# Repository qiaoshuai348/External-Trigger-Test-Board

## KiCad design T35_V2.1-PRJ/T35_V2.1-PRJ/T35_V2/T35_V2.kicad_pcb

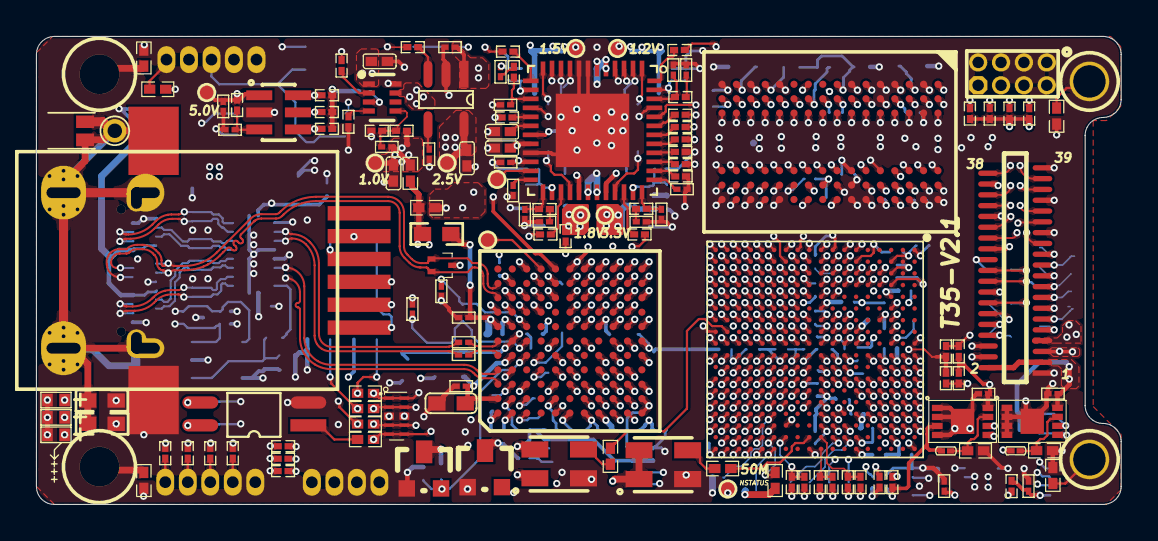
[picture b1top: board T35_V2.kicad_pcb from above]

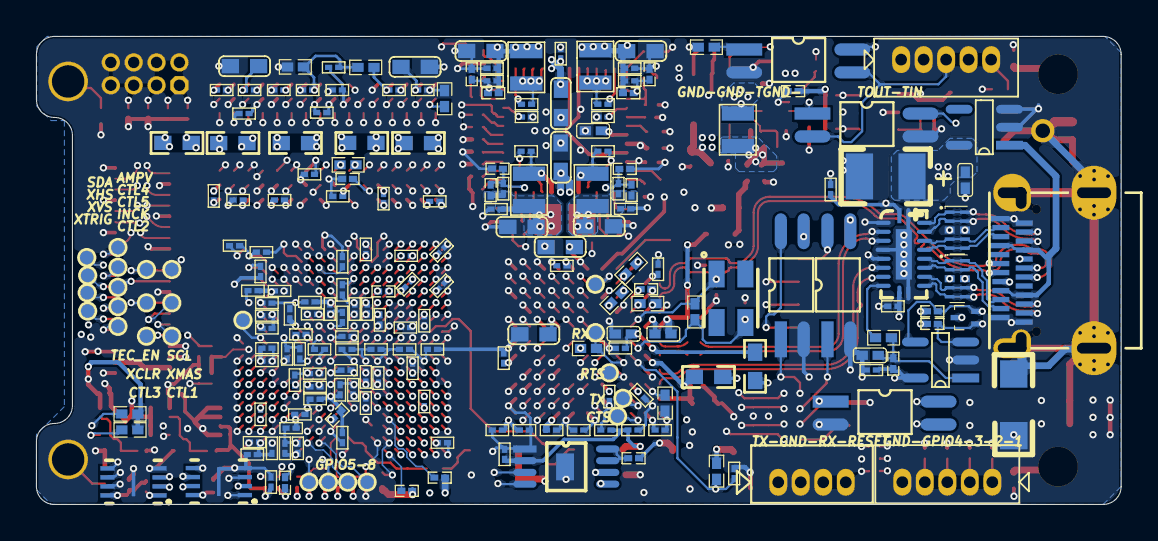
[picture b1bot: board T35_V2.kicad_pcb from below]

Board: 12 copper layers, 60.3 x 26.0 mm, 356 parts (217 on the bottom side), 287 nets.

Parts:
C1, C3, C83, C87, C91, C96: 22pF/6.3V; 0201CS
C2, C4, C7, C9, C11, C14, C16, C18, C22, C25, C28, C30, C31, C33, C35, C38, C39, C42, C43, C45, C47, C49, C52, C55, C58, C63, C66, C68, C77, C80, C85, C88, C93, C94, C98, C99, C104, C111, C112, C113, C115, C117, C119, C120, C123, C125, C127, C128, C129, C130, C131, C134, C135, C136, C137, C138, C139, C140, C141, C154, C155, C156, C157, C158, C159: 100nF/10V; 0201CS
C5, C12, C19, C20, C23, C26, C36, C40, C44, C46, C48, C50, C53, C56, C59, C61, C64: 2.2uF/6.3V; 0201CS
C6, C8, C10, C13, C15, C17, C21, C24, C27, C34, C37, C41, C51, C54, C57, C60, C62, C65, C75, C102: 10nF/16V; 0201CS
C29, C73, C142, C143, C144, C145: 1uF/6.3V; 0201CS
C32, C71, C105, C106: 10uF/6.3V; 0402CS
C67, C72, C110, C122, C126: 4.7uF/6.3V; 0402CS
C69, C70: 22uF/10V; 0603CS
C74: 1nF/6.3V; 0201CS
C76, C79: 33nF/6.3V; 0201CS
C78, C86, C95, C100, C124, C132, C133: 22uF/6.3V; 0603CS
C81, C89, C97, C101: 68pF/6.3V; 0201CS
C82, C84, C90, C92: 4.7nF/6.3V; 0201CS
C103: 10pF/6.3V; 0201CS
C107, C118, C121: 18pF/6.3V; 0201CS
C114: 470pF/2KV; 1206CS
C116: 33pF/6.3V; 0402CS
C146, C147: 47uF/6.3V; 0603CS
C148, C149, C150, C151, C152, C153: 10nF/6.3V; 0201CS
CRY1: 19.2MHZ无源晶振; XTAL_SMD_SMALL
ECP1: 47uF10V; CASE-B
FB1, FB2, FB3, FB4, FB5: FB 600Ω@100MHz; FB0603
FB6: FB*; FB0603
FB7, FB8, FB9: FB 1.8KΩ@100MHz; FB0603
L1, L2, L3, L4: 2.2uH/1.5A; 201610
L5: 0.47uH; 201610
LED1: LED_R; 0402LED
LED2: LED_G; 0402LED
LED3: LED_B; 0402LED
P1: USB3.0_Type-C; CONN_105450-0101_MOL - ENFORCE
P2: 39Pin_MIPI_Connector; 39PIN_0.3错位排序
P3, P5: 1.25mm5Pin; CC125-5
P4: GuiderPort; RJ11-SMD
P6: 1.25mm4Pin; CON_530470410_MOL
P7: JTAG-1.25mm2*4; MHDR2X4
P8: M543-1
PAD1, PAD2: PAD; M2-R4-NC
PAD3, PAD4: PAD; M1.6-R3.2-NC
R1, R2: 33Ω; 0402RS
R3, R5, R6, R7, R8, R9, R10, R12, R15, R16, R17, R18, R20, R21, R22, R25, R26, R28, R30, R31, R32, R36, R40, R43, R44, R46, R50, R51, R53, R67, R84, R93, R101, R102, R103, R104: 10K; 0201RS
R4: 324K; 0402RS
R11, R13, R14, R19, R23: 10K*; 0201RS
R24: 44.2K; 0201RS
R27, R29: 0Ω; 0201RS
R33: 22K; 0201RS
R34: 4.99K; 0201RS
R35, R37, R39, R41: 15.4K; 0201RS
R38: 8.66K; 0201RS
R42: 12.4K; 0201RS
R45: 30.9K; 0201RS
R47, R48, R49: 100K; 0201RS
R52, R57: 0*; 0201RS
R54: 20K; 0201RS
R55: 91K; 0201RS
R56: 30K; 0201RS
R58: 1M; 0603RS
R59, R60, R69, R71, R72: 1.5K; 0402RS
R61: 200 1%; 0402RS
R62: 6.04K 1%; 0402RS
R64, R65: 5.1K; 0201RS
R66: 10Ω; 0402RS
R68: 1.5K*; 0402RS
R70: 200K; 0201RS
R74: 1MΩ*; 0402RS
R75, R79, R80, R88: 1K 1%; 0402RS
R76, R77, R86, R87, R96, R97: 0*; 0402RS
R78: 80.6Ω 1%; 0402RS
R81: 4.7K; 0402RS
R82, R83: 240 1%; 0201RS
R89, R90, R91, R92, R94, R95: 100; 0402RS
R98: 300; 0201RS
R99, R100: 100; 0201RS
SJ1, SJ2: SolderableJumper*; SJ
T1, T2, T3, T4, T5, T6, T8, T9, T10, T11, T12, T13, T14, T15, T16, T17, T18, T19, T20, T21, T22, T23, T24, T25, T26, T27, T28, T29, T30, T31, T32, T33, T34, T35, T36: TP-S
U1: T35F324; T35-F324-BGA100P9X9-81A
U2: 50MHz; XTAL_SMD_SMALL
U3: 100MHz; XTAL_SMD_SMALL
U4, U14: MAX809TTRG; MAX809
U5, U19: GD25Q32EEIGR; SON127P600-8N-USON8
U6: TPS65400RGZT; QFN50P700X700X100-49N_TPS65400RGZT(PRIMARY)
U7: TPS628501DRLR; SOT583
U8: TPS79325DBVR; SOT-23-5
U9: LM3880MF-1AA; SOT-23-6
U10: CYUSB3014-BZXI; CYUSB3014
U11: NCP361SNT1G; SOT-23-5
U12, U30: TPD2EUSB30ADRTR-N; DRT0003A
U13: TLV3201AIDBVR; sot-23-5
U15: UM3212M8; MSOP8
U16: BL24C64A-NTRC; UDFN-8LL
U17: MT41K256M16TW-107:P; MICT-TNA-96
U18: BL24CM1A-NTRC; UDFN-8LL
U20, U22, U23, U24, U25, U26: IS281GB; TLP281-1
U21, U28, U29: RCLAMP0524
U27: CBTL02043ABQ; VQFN-20

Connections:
A0: U1.U15, U10.H5
A1: U1.T17, U10.J5
AMPV: P2.23, T22.1, U1.B10
CBSEL0: R13.2, R20.2, U1.J17
CBSEL1: R14.2, R22.2, U1.J18
CBUS0: R10.2, R19.2, U1.M14
CBUS1: R11.2, R21.2, U1.M16
CBUS2: R12.2, R23.2, U1.M17
CC1: P1.A5, R65.2, U13.3, U30.1
CC2: P1.B5, R64.2, U13.4, U30.2
CCK: U1.N13, U5.6, U19.6
CDI0: U1.M13, U5.5, U19.5
CDI1: U1.N14, U5.2, U19.2
CDI2: R9.1, U1.K14, U5.3, U19.3
CDI3: R5.1, U1.K18, U5.7, U19.7
CDONE: R3.2, U1.N18
CHARGER_DECT: T21.1, U10.D11
CLK_50MHz: R1.2, U1.K17
CLK_OUT: R53.1, U6.44, U7.3
CMOS_CTL1: P2.10, T31.1, U1.B12
CMOS_CTL2: P2.9, T33.1, U1.B16
CMOS_CTL3: P2.8, T35.1, U1.A13
CMOS_CTL4: P2.19, T30.1, U1.A12
CMOS_CTL5: P2.18, T32.1, U1.B11
CRESET_N: P7.8, R4.2, U1.N17, U4.2
CSI: R6.2, U1.N15
CTL1: U1.R13, U10.K7
CTL4: U1.V10, U10.G7
CTL5: U1.U14, U10.G6
CTL6: U1.V16, U10.K6
CTL7: U1.P12, U10.H8
DDR_A0: U1.P3, U17.N3
DDR_A1: U1.P4, U17.P7
DDR_A2: U1.R6, U17.P3
DDR_A3: U1.P6, U17.N2
DDR_A4: U1.T1, U17.P8
DDR_A5: U1.R3, U17.P2
DDR_A6: U1.R7, U17.R8
DDR_A7: U1.V8, U17.R2
DDR_A8: U1.T4, U17.T8
DDR_A9: U1.T3, U17.R3
DDR_A10: U1.V7, U17.L7
DDR_A11: U1.U7, U17.R7
DDR_A12: U1.U6, U17.N7
DDR_A13: U1.T6, U17.T3
DDR_A14: U1.V6, U17.T7
DDR_A15: U1.V5, U17.M7
DDR_BA0: U1.T5, U17.M2
DDR_BA1: U1.U3, U17.N8
DDR_BA2: U1.R5, U17.M3
DDR_CKE: U1.N7, U17.K9
DDR_CK_N: R78.1, U1.R1, U17.K7
DDR_CK_P: R78.2, U1.P1, U17.J7
DDR_DM0: U1.L1, U17.E7
DDR_DM1: U1.H5, U17.D3
DDR_DQ0: U1.N4, U17.E3
DDR_DQ1: U1.N2, U17.F7
DDR_DQ2: U1.N1, U17.F2
DDR_DQ3: U1.M2, U17.F8
DDR_DQ4: U1.M4, U17.H3
DDR_DQ5: U1.L3, U17.H8
DDR_DQ6: U1.K1, U17.G2
DDR_DQ7: U1.L4, U17.H7
DDR_DQ8: U1.J1, U17.D7
DDR_DQ9: U1.K2, U17.C3
DDR_DQ10: U1.J3, U17.C8
DDR_DQ11: U1.K3, U17.C2
DDR_DQ12: U1.J4, U17.A7
DDR_DQ13: U1.H4, U17.A2
DDR_DQ14: U1.J5, U17.B8
DDR_DQ15: U1.G4, U17.A3
DDR_DQS0_N: U1.N3, U17.G3
DDR_DQS0_P: U1.M3, U17.F3
DDR_DQS1_N: U1.L5, U17.B7
DDR_DQS1_P: U1.K5, U17.C7
DDR_ODT: U1.U1, U17.K1
DDR_REFCLK: R2.2, U1.U8
DDR_RST: R81.1, U1.T2, U17.T2
DDR_~CAS: U1.V2, U17.K3
DDR_~CS: U1.N6, U17.L2
DDR_~RAS: U1.V3, U17.J3
DDR_~WE: U1.U4, U17.L3
D_N: P1.A7, P1.B7, U10.A10, U12.1
D_P: P1.A6, P1.B6, U10.A9, U12.2
FLASH_CS: R84.1, U1.G16, U19.1
FPGA_TCK: P7.1, R15.2, U1.T16
FPGA_TDI: P7.3, R17.2, U1.R16
FPGA_TDO: P7.7, R16.2, U1.P17
FPGA_TMS: P7.5, R18.2, U1.P16
FX3_RESET: C117.1, R68.2, U1.D13, U10.C5, U14.2
GND: C1.1, C2.2, C3.1, C4.2, C5.2, C6.2, C7.2, C8.2, C9.2, C10.2, C11.2, C12.2, C13.2, C14.2, C15.2, C16.2, C17.2, C18.2, C19.2, C20.2, C21.2, C22.2, C23.2, C24.2, C25.2, C26.2, C27.2, C28.2, C29.2, C30.2, C31.2, C32.2, C33.2, C34.2, C35.2, C36.2, C37.2, C38.2, C39.2, C40.2, C41.2, C42.2, C43.2, C44.2, C45.2, C46.2, C47.2, C48.2, C49.2, C50.2, C51.2, C52.2, C53.2, C54.2, C55.2, C56.2, C57.2, C58.2, C59.2, C60.2, C61.2, C62.2, C63.2, C64.2, C65.2, C66.2, C67.2, C68.1, C69.1, C70.1, C71.2, C72.2, C73.1, C74.1, C75.1, C76.1, C77.1, C78.2, C79.1, C82.2, C83.2, C84.2, C85.1, C86.2, C87.2, C90.2, C91.2, C92.2, C94.1, C95.2, C96.2, C99.1, C100.2, C102.2, C104.2, C105.2, C106.2, C107.2, C110.1, C112.1, C114.1, C115.1, C116.2, C117.2, C118.1, C119.2, C120.1, C121.2, C122.1, C123.1, C124.1, C125.1, C126.1, C127.1, C128.1, C129.1, C130.1, C131.1, C132.1, C133.1, C134.1, C135.1, C136.1, C137.1, C138.2, C139.2, C140.2, C141.2, C142.2, C143.2, C144.2, C145.2, C146.2, C147.2, C148.2, C149.2, C150.2, C151.2, C152.2, C153.2, C155.2, C156.2, C157.2, C158.1, C159.1, ECP1.2, FB6.1, LED1.2, LED2.2, LED3.2, P1.A1, P1.A12, P1.B1, P1.B12, P2.1, P2.4, P2.6, P2.16, P2.24, P2.27, P2.30, P2.33, P2.36, P2.39, P3.5, P4.0, P5.1, P5.2, P6.2, P7.6, R19.1, R20.1, R21.1, R22.1, R23.1, R24.1, R33.2, R36.2, R40.2, R44.2, R46.2, R55.1, R56.1, R57.1, R58.2, R61.2, R62.2, R64.1, R65.1, R75.2, R80.1, R81.2, R82.2, R83.2, R86.1, R87.1, R88.2, R96.1, R97.1, R101.2, R102.2, R103.2, R104.2, U1.A1, U1.A18, U1.C3, U1.C7, U1.C8, U1.C12, U1.C15, U1.D10, U1.F2, U1.F4, U1.F17, U1.G7, U1.G9, U1.G11, U1.H1, U1.H8, U1.H10, U1.H12, U1.J7, U1.J9, U1.J11, U1.J16, U1.K8, U1.K10, U1.K12, U1.L7, U1.L9, U1.L11, U1.M1, U1.M5, U1.M8, U1.M10, U1.M12, U1.N16, U1.P7, U1.R2, U1.R4, U1.R10, U1.T13, U1.V1, U1.V4, U1.V18, U2.2, U3.2, U4.1, U5.4, U5.9, U6.7, U6.8, U6.21, U6.EP, U7.8, U8.2, U9.2, U10.A1, U10.A8, U10.B2, U10.B4, U10.B7, U10.B8, U10.B9, U10.D8, U10.E2, U10.E6, U10.G1, U10.G11, U10.K3, U10.K4, U10.K8, U10.L1, U10.L2, U10.L3, U10.L6, U10.L11, U11.2, U11.3, U12.3, U13.2, U14.1, U15.1, U15.SS, U16.1, U16.2, U16.3, U16.4, U16.9, U17.A9, U17.B1, U17.B3, U17.B9, U17.D1, U17.D8, U17.E1, U17.E2, U17.E8, U17.F9, U17.G1, U17.G8, U17.G9, U17.J2, U17.J8, U17.M1, U17.M9, U17.P1, U17.P9, U17.T1, U17.T9, U18.1, U18.2, U18.4, U18.9, U19.4, U19.9, U20.2, U21.9, U21.10, U22.2, U23.2, U24.2, U25.3, U26.2, U27.2, U27.5, U27.11, U27.20, U27.21, U28.9, U28.10, U29.9, U29.10, U30.3
GPIO1_IO: P3.1, R89.2, R104.1, U1.C13, U21.1, U21.8
GPIO2_IO: P3.2, R90.2, R103.1, U1.E15, U21.2, U21.7
GPIO3_IO: P3.3, R91.2, R102.1, U1.E14, U21.3, U21.6
GPIO4_IO: P3.4, R92.2, R101.1, U1.D14, U21.4, U21.5
GPIO5: T2.1, U1.D12
GPIO6: T3.1, U1.E12
GPIO7: T4.1, U1.G17
GPIO8: T5.1, U1.H17
Guider_DEC+: P4.4, U23.4
Guider_DEC-: P4.5, U24.4
Guider_RA+: P4.3, U22.4
Guider_RA-: P4.6, U20.4
I2CSCL: P2.22, R72.2, T24.1, U1.A9, U15.3, U16.6
I2CSCL_33: R29.2, R59.2, U10.D9, U15.6, U18.6
I2CSDA: P2.21, R71.2, T26.1, U1.A10, U15.4, U16.5
I2CSDA_33: R27.2, R60.2, U10.D10, U15.5, U18.5
INCK: P2.13, T25.1, U1.B15
LED_B: R100.1, U1.H16
LED_G: R99.1, U1.H15
LED_R: R98.1, U1.G15
MIPI_D1_N: P2.34, U1.F1
MIPI_D1_P: P2.35, U1.G1
MIPI_D2_N: P2.28, U1.E3
MIPI_D2_P: P2.29, U1.D3
MIPI_D3_N: P2.37, U1.H2
MIPI_D3_P: P2.38, U1.G2
MIPI_D4_N: P2.25, U1.E4
MIPI_D4_P: P2.26, U1.D4
MIPI_DCK_A_N: P2.31, U1.G3
MIPI_DCK_A_P: P2.32, U1.F3
NSTATUS: T8.1, U1.J14
NetC71_1: C71.1, U6.18
NetC74_2: C74.2, U6.45
NetC75_2: C75.2, U6.16
NetC76_2: C76.2, U6.24
NetC79_2: C79.2, U6.37
NetC80_1: C80.1, L1.1, U6.2, U6.3, U6.4
NetC80_2: C80.2, U6.1
NetC81_2: C81.2, R34.1, R36.1, U6.47
NetC82_1: C82.1, R35.2
NetC83_1: C83.1, R35.1, U6.46
NetC84_1: C84.1, R37.2
NetC87_1: C87.1, R37.1, U6.15
NetC88_1: C88.1, L2.1, U6.9, U6.10, U6.11
NetC88_2: C88.2, U6.12
NetC89_2: C89.2, R38.1, R40.1, U6.14
NetC90_1: C90.1, R39.2
NetC91_1: C91.1, R39.1, U6.25
NetC92_1: C92.1, R41.2
NetC93_1: C93.1, L3.1, U6.29
NetC93_2: C93.2, U6.28
NetC96_1: C96.1, R41.1, U6.36
NetC97_2: C97.2, R42.1, R44.1, U6.26
NetC98_1: C98.1, L4.1, U6.32
NetC98_2: C98.2, U6.33
NetC101_2: C101.2, R45.1, R46.1, U6.35
NetC102_1: C102.1, U8.4
NetC103_2: C103.2, R54.1, R56.2, U7.5
NetC107_1: C107.1, R52.2, U9.3
NetC116_1: C116.1, R66.1, R67.2, U13.1
NetC118_2: C118.2, CRY1.3, R74.1, U10.C6
NetC121_1: C121.1, CRY1.1, R74.2, U10.C7
NetL5_1: L5.1, U7.7
NetLED1_1: LED1.1, R98.2
NetLED2_1: LED2.1, R99.2
NetLED3_1: LED3.1, R100.2
NetP1_A4: P1.A4, P1.A9, P1.B4, P1.B9, U11.1
NetPAD1_1: PAD1.1, R96.2
NetPAD2_1: PAD2.1, R97.2
NetPAD3_1: PAD3.1, R86.2
NetPAD4_1: PAD4.1, R87.2
NetR1_1: R1.1, U2.3
NetR2_1: R2.1, U3.3
NetR25_2: R25.2, U6.39
NetR26_2: R26.2, U6.48
NetR27_1: R27.1, U6.42
NetR28_2: R28.2, U6.13
NetR29_1: R29.1, U6.43
NetR30_2: R30.2, U6.27
NetR31_1: R31.1, U6.41
NetR32_2: R32.2, U6.34
NetR33_1: R33.1, U6.38
NetR43_2: R43.2, U6.17
NetR50_2: R50.2, U7.2
NetR51_2: R51.2, U8.3
NetR55_2: R55.2, U7.4
NetR57_2: R57.2, U10.C9
NetR61_1: R61.1, U10.B3
NetR62_1: R62.1, U10.C8
NetR66_2: R66.2, U27.9
NetR70_1: R70.1, U15.7, U15.8
NetR75_1: R75.1, SJ2.2, U16.7
NetR82_1: R82.1, U17.L8
NetR83_1: R83.1, U1.N5
NetR88_1: R88.1, SJ1.2, U18.7
NetR89_1: R89.1, U20.1
NetR90_1: R90.1, U22.1
NetR91_1: R91.1, U23.1
NetR92_1: R92.1, U24.1
NetR94_1: R94.1, U25.1
NetR95_1: R95.1, U26.1
NetT9_1: T9.1, U6.23
PCLK: U1.U12, U10.J6
PLLIN0: T6.1, U1.C9
POWER_ON_1: R26.1, R47.1, R50.1, U9.6
POWER_ON_2: R28.1, R30.1, R32.1, R48.1, U9.5
POWER_ON_3: R49.1, R51.1, U9.4
RX1_N: P1.B10, U27.13, U28.3, U28.6
RX1_P: P1.B11, U27.12, U28.4, U28.5
RX2_N: P1.A10, U27.16, U29.4, U29.5
RX2_P: P1.A11, U27.17, U29.3, U29.6
SSRX_N: U10.A3, U27.8
SSRX_P: U10.A4, U27.7
SSTX_N: C111.2, U27.3
SSTX_P: C113.2, U27.4
SS_N: R7.2, U1.P15, U5.1
SYNC: R24.2, U6.40
TEC_EN: P2.20, T28.1, U1.A11
TEST_N: R8.2, U1.J15
TRIG_GND1: P5.3, U25.2, U26.3
TRIG_GND2: P4.2, U20.3, U22.3, U23.3, U24.3
TRIG_IN: P5.5, R94.2
TRIG_IN_IO: R93.2, U1.D11, U25.4
TRIG_OUT: P5.4, U26.4
TRIG_OUT_IO: R95.2, U1.C11
TX1_N: P1.A3, U27.15, U28.1, U28.8
TX1_P: P1.A2, U27.14, U28.2, U28.7
TX2_N: P1.B3, U27.18, U29.2, U29.7
TX2_P: P1.B2, U27.19, U29.1, U29.8
UART_CTS: T17.1, U10.C1
UART_RTS: T16.1, U10.D4
UART_RX_FPGA: P6.3, U1.D16
UART_RX_FX3: R69.2, T19.1, U1.E13, U10.D5
UART_TX_FPGA: P6.1, U1.C16
UART_TX_FX3: T18.1, U1.F13, U10.C2
UD0: U1.N12, U10.F10
UD1: U1.R12, U10.F9
UD2: U1.V12, U10.F7
UD3: U1.N11, U10.G10
UD4: U1.U10, U10.G9
UD5: U1.T11, U10.F8
UD6: U1.P10, U10.H10
UD7: U1.P11, U10.H9
UD8: U1.N9, U10.J10
UD9: U1.P9, U10.J9
UD10: U1.U9, U10.K11
UD11: U1.V9, U10.L10
UD12: U1.T9, U10.K10
UD13: U1.R9, U10.K9
UD14: U1.N10, U10.J8
UD15: U1.U11, U10.G8
UD16: U1.P14, U10.K2
UD17: U1.P13, U10.J4
UD18: U1.R17, U10.K1
UD19: U1.R15, U10.J2
UD20: U1.R14, U10.J3
UD21: U1.P18, U10.J1
UD22: U1.R18, U10.H2
UD23: U1.V15, U10.H3
UD24: U1.T15, U10.F4
UD25: U1.U18, U10.G2
UD26: U1.V13, U10.G3
UD27: U1.U16, U10.F3
UD28: U1.U13, U10.F5
UD29: U1.T18, U10.E1
UD30: U1.T12, U10.E5
UD31: U1.V14, U10.E4
USBType-C-SHELL: C114.2, FB6.2, P1.SH1, P1.SH2, P1.SH3, P1.SH4, P8.0, R58.1
USB_RESET: P6.4, U1.D15
VBATT: T20.1, U10.E10
VCC1V0: C103.1, C105.1, L5.2, R54.2, R77.2, T14.1
VCC1V0A_PLL: C122.2, C123.2, FB7.2, U10.A7
VCC1V0A_USB: C124.2, C125.2, FB8.2, U10.A2, U10.B5
VCC1V2: C5.1, C6.1, C7.1, C8.1, C9.1, C10.1, C11.1, C12.1, C13.1, C14.1, C15.1, C16.1, C17.1, C18.1, C77.2, C78.1, C81.1, FB1.1, FB2.1, FB3.1, FB4.1, FB5.1, L1.2, R34.2, R76.2, T10.1, U1.G8, U1.G10, U1.G12, U1.H7, U1.H9, U1.H11, U1.J8, U1.J10, U1.J12, U1.K7, U1.K9, U1.K11, U1.L8, U1.L10, U1.L12, U1.M7, U1.M9, U1.M11
VCC1V2_BL: C30.1, FB3.2, U1.F12
VCC1V2_BR: C33.1, FB4.2, U1.N8, U1.P8
VCC1V2_MIPI_RX: C23.1, C24.1, C25.1, FB2.2, U1.C5, U1.H3
VCC1V2_MIPI_TX: C20.1, C21.1, C22.1, FB1.2, U1.C2, U1.C6
VCC1V2_TR: C34.1, C35.1, FB5.2, U1.F8, U1.F9
VCC1V5: C36.1, C37.1, C38.1, C39.1, C40.1, C41.1, C42.1, C43.1, C85.2, C86.1, C89.1, C138.1, C139.1, C140.1, C141.1, C142.1, C143.1, C144.1, C145.1, C146.1, C147.1, C148.1, C149.1, C150.1, C151.1, C152.1, C153.1, C154.1, L2.2, R38.2, R79.2, T11.1, U1.J2, U1.K4, U1.L2, U1.L6, U1.P2, U1.P5, U1.T7, U1.U2, U1.U5, U17.A1, U17.A8, U17.B2, U17.C1, U17.C9, U17.D2, U17.D9, U17.E9, U17.F1, U17.G7, U17.H2, U17.H9, U17.K2, U17.K8, U17.N1, U17.N9, U17.R1, U17.R9
VCC1V8: C3.2, C4.1, C50.1, C51.1, C52.1, C56.1, C57.1, C58.1, C59.1, C60.1, C94.2, C95.1, C97.1, C119.1, C120.2, L3.2, P2.2, P2.3, R42.2, R71.1, R72.1, R93.1, SJ2.1, T12.1, U1.C10, U1.C14, U1.E10, U1.F15, U1.J6, U3.1, U3.4, U15.2, U16.8
VCC2V5: C26.1, C27.1, C28.1, C106.1, T15.1, U1.C4, U1.D7, U8.5
VCC3V3: C1.2, C2.1, C19.1, C31.1, C44.1, C45.1, C46.1, C47.1, C48.1, C49.1, C53.1, C54.1, C55.1, C61.1, C62.1, C63.1, C64.1, C65.1, C66.1, C99.2, C100.1, C101.1, C112.2, C115.2, C128.2, C129.2, C130.2, C131.2, C132.2, C157.1, C158.2, C159.2, FB9.1, L4.2, P2.5, P7.2, R3.1, R4.1, R5.2, R6.1, R7.1, R8.1, R9.2, R10.1, R11.1, R12.1, R13.1, R14.1, R15.1, R16.1, R17.1, R18.1, R45.2, R59.1, R60.1, R67.1, R68.1, R69.1, R70.2, R84.2, SJ1.1, T13.1, U1.C17, U1.F18, U1.J13, U1.K13, U1.L13, U1.R11, U1.T10, U1.T14, U1.U17, U2.1, U2.4, U4.3, U5.8, U10.B1, U10.C11, U10.E3, U10.F1, U10.H4, U10.H7, U10.H11, U10.J7, U10.L9, U13.5, U14.3, U18.3, U18.8, U19.8, U27.1, U27.6, U27.10
VCC3V3IOUSB: C126.2, C127.2, FB9.2, U10.B6
VCC5V: C29.1, C32.1, C68.2, C69.2, C70.2, C73.2, C104.1, C110.2, ECP1.1, P2.7, R52.1, T1.1, U6.5, U6.6, U6.22, U6.30, U6.31, U7.1, U8.1, U9.1, U10.E11, U11.5
VCCFX3: C133.2, C134.2, C135.2, C136.2, C137.2, FB7.1, FB8.1, R76.1, R77.1, U10.B10, U10.C3, U10.E9, U10.F11, U10.H1, U10.J11, U10.L5, U10.L7
VDDA: C72.1, U6.19
VDDD: C67.1, R25.1, R31.2, R43.1, R47.2, R48.2, R49.2, R53.2, U6.20
VDD_DDR_VREF: C154.2, C155.1, C156.1, R79.1, R80.2, U1.M6, U17.H1, U17.M8
XCLR: P2.14, T23.1, U1.A14
XHS: P2.17, T34.1, U1.B14
XMASTER: P2.12, T27.1, U1.B13
XTRIG: P2.11, T29.1, U1.A16
XVS: P2.15, T36.1, U1.A15
aa_N: C111.1, U10.A6
aa_P: C113.1, U10.A5
